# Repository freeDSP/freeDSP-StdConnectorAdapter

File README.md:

# freeDSPx Adapter

BOARD STATUS: READY TO BE BUILT

MAIN COORDINATOR: [ssMMnn](https://github.com/ssMMnn)

Adapter for the freeDSP Classic. Adapts the old expansion pinheader to I2S standard connectors. Generates masterclock. 

## License

This work and all other materials under https://github.com/freeDSP are licensed under a <a rel="license" href="http://creativecommons.org/licenses/by-sa/4.0/legalcode">Creative Commons Attribution Share-Alike 4.0 license</a>. This allows for both personal and commercial derivative works, as long as they credit freeDSP and release their designs under the same license.

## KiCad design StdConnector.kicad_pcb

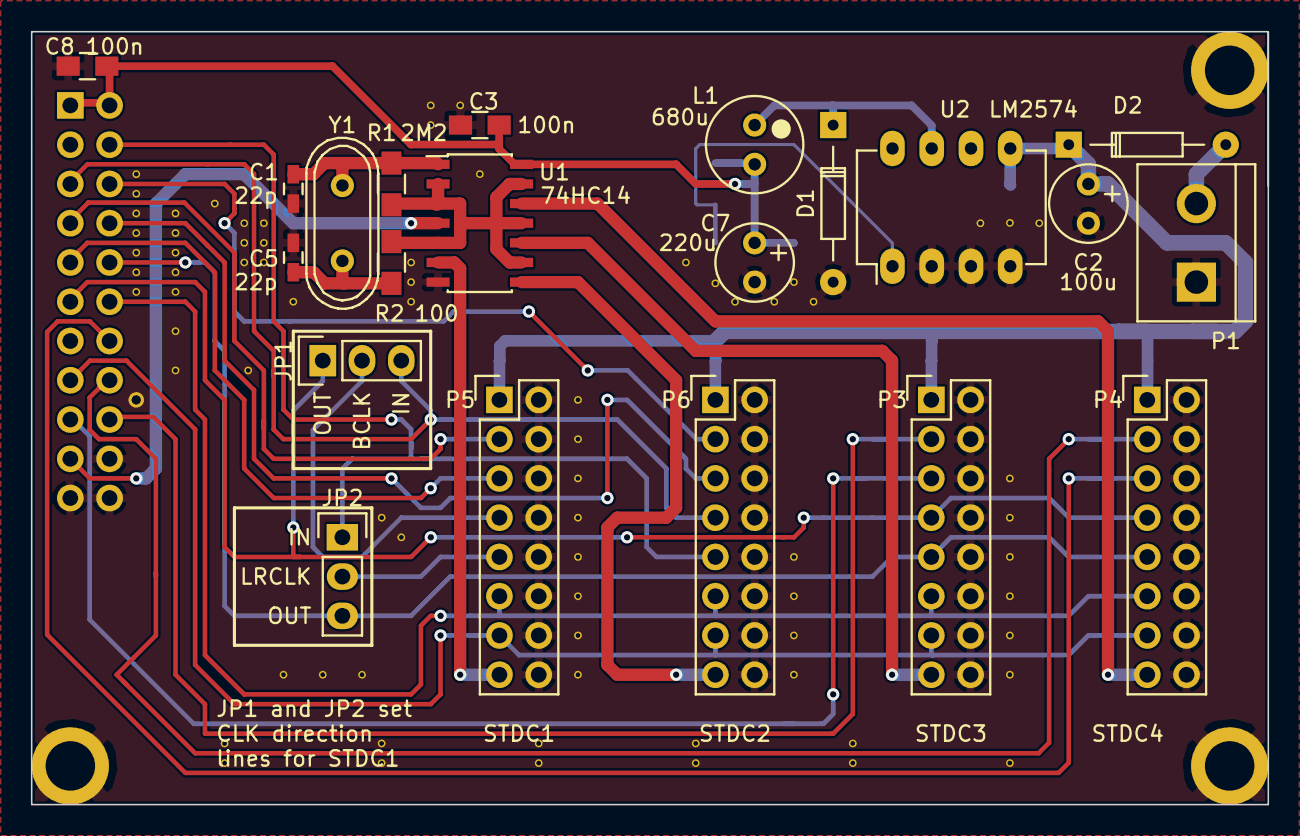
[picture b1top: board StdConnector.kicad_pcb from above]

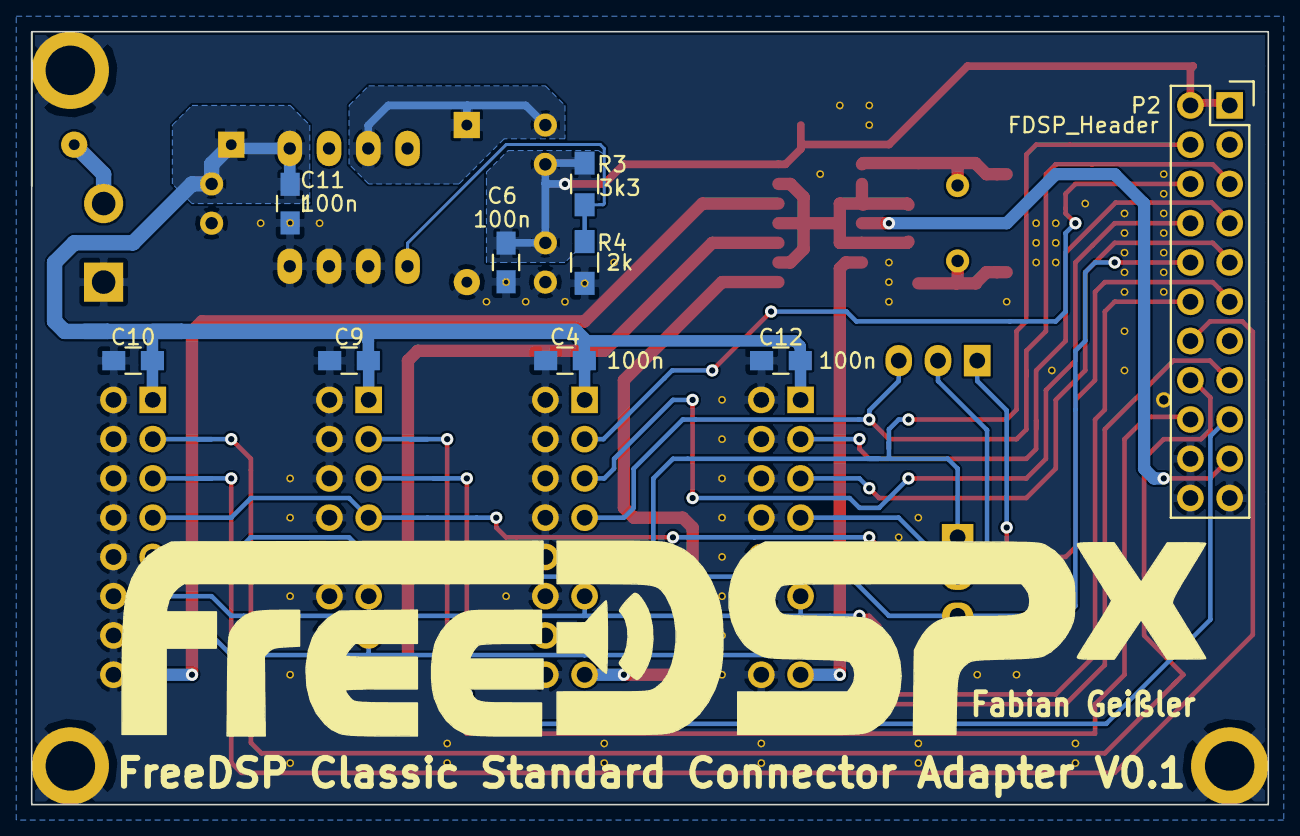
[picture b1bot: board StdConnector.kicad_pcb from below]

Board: 2 copper layers, 80.0 x 50.0 mm, 30 parts (9 on the bottom side), 30 nets.

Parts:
C1, C5: 22p; C_0603_HandSoldering
C2: 100u; Elko_vert_11x5mm_RM2.5_CopperClear
C3, C4, C6, C8, C9, C10, C11, C12: 100n; C_0805_HandSoldering
C7: 220u; Elko_vert_11x5mm_RM2.5_CopperClear
D1, D2: D_Schottky; Diode_DO-35_SOD27_Horizontal_RM10
JP1, JP2: JUMPER3; Pin_Header_Straight_1x03
L1: 680u; Elko_vert_11.2x6.3mm_RM2.5_CopperClear
P1: CONN_01X02; bornier2
P2: FDSP_Header; Socket_Strip_Straight_2x11
P3: StdConn_ClkOut; Pin_Header_Straight_2x08
P4: StsConn_ClkOut; Pin_Header_Straight_2x08
P5: StdConn_ClkVar; Pin_Header_Straight_2x08
P6: StdConn_ClkIn; Pin_Header_Straight_2x08
R1: 2M2; R_0805_HandSoldering
R2: 100; R_0805_HandSoldering
R3: 3k3; R_0805_HandSoldering
R4: 2k; R_0805_HandSoldering
U1: 74HC14; SOIC-14_3.9x8.7mm_Pitch1.27mm
U2: LM2574; DIP-8_W7.62mm_LongPads
Y1: 12.288MHz; Crystal_HC49-U_Vertical

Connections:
+12V: C2.1, C4.1, C9.1, C10.1, C11.1, C12.1, D2.1, P3.1, P4.1, P5.1, P6.1, U2.5
/BCLK_IN: JP1.3, P2.5, P6.7
/BCLK_OUT: JP1.1, P2.11, P3.7, P4.7
/CLK0: P5.15, U1.6
/CLK1: P6.15, U1.8
/CLK2: P3.15, U1.10
/CLK3: P4.15, U1.12
/LRCLK_IN: JP2.1, P2.4, P6.9
/LRCLK_OUT: JP2.3, P2.10, P3.9, P4.9
/MCLK: P2.19, U1.4
/MDI0: P2.7, P5.3
/MDI1: P2.6, P6.3
/MDI2: P2.18, P3.3
/MDI3: P2.16, P4.3
/MDO0: P2.9, P5.5
/MDO1: P2.8, P6.5
/MDO2: P2.17, P3.5
/MDO3: P2.14, P4.5
/SCL: P2.15, P3.13, P4.13, P5.13, P6.13
/SDA: P2.12, P3.11, P4.11, P5.11, P6.11
GND: C1.1, C2.2, C3.2, C4.2, C5.1, C6.2, C7.2, C8.2, C9.2, C10.2, C11.2, C12.2, D1.2, P1.1, P2.20, P2.21, P2.22, P3.2, P3.4, P3.6, P3.8, P3.10, P3.12, P3.14, P3.16, P4.2, P4.4, P4.6, P4.8, P4.10, P4.12, P4.14, P4.16, P5.2, P5.4, P5.6, P5.8, P5.10, P5.12, P5.14, P5.16, P6.2, P6.4, P6.6, P6.8, P6.10, P6.12, P6.14, P6.16, R4.2, U1.7, U2.2, U2.3, U2.4
unnamed: C1.2, R1.2, U1.1, Y1.1
unnamed: C5.2, R2.2, Y1.2
unnamed: D1.1, L1.1, U2.7
unnamed: D2.2, P1.2
unnamed: JP1.2, P5.7
unnamed: JP2.2, P5.9
unnamed: R1.1, R2.1, U1.2, U1.3, U1.5, U1.9, U1.11, U1.13
unnamed: R3.2, R4.1, U2.1
VCC: C3.1, C6.1, C7.1, C8.1, L1.2, P2.1, P2.2, R3.1, U1.14

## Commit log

2016-05-10 files added
2016-05-10 Changed layout for clock lines impedance fitting to 50 ohm.
2016-05-12 Changed Connector position to fit old board. HF Lines optimized.
2016-05-14 Made all GND VIAs equal size.
2016-05-15 Small Changes
2016-05-15 Corrected resistor value error in stepdown feedback.
2016-05-16 Added License.
2016-05-16 Little Changes, added Gerber files.
2016-05-30 Added BOM
2017-02-28 Deleted non funtional Adapter
2017-02-28 Global Commit
